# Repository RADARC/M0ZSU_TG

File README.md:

# M0ZSU_TG

Homebrew tracking generator for HP 8558B Spectrum Analyser.

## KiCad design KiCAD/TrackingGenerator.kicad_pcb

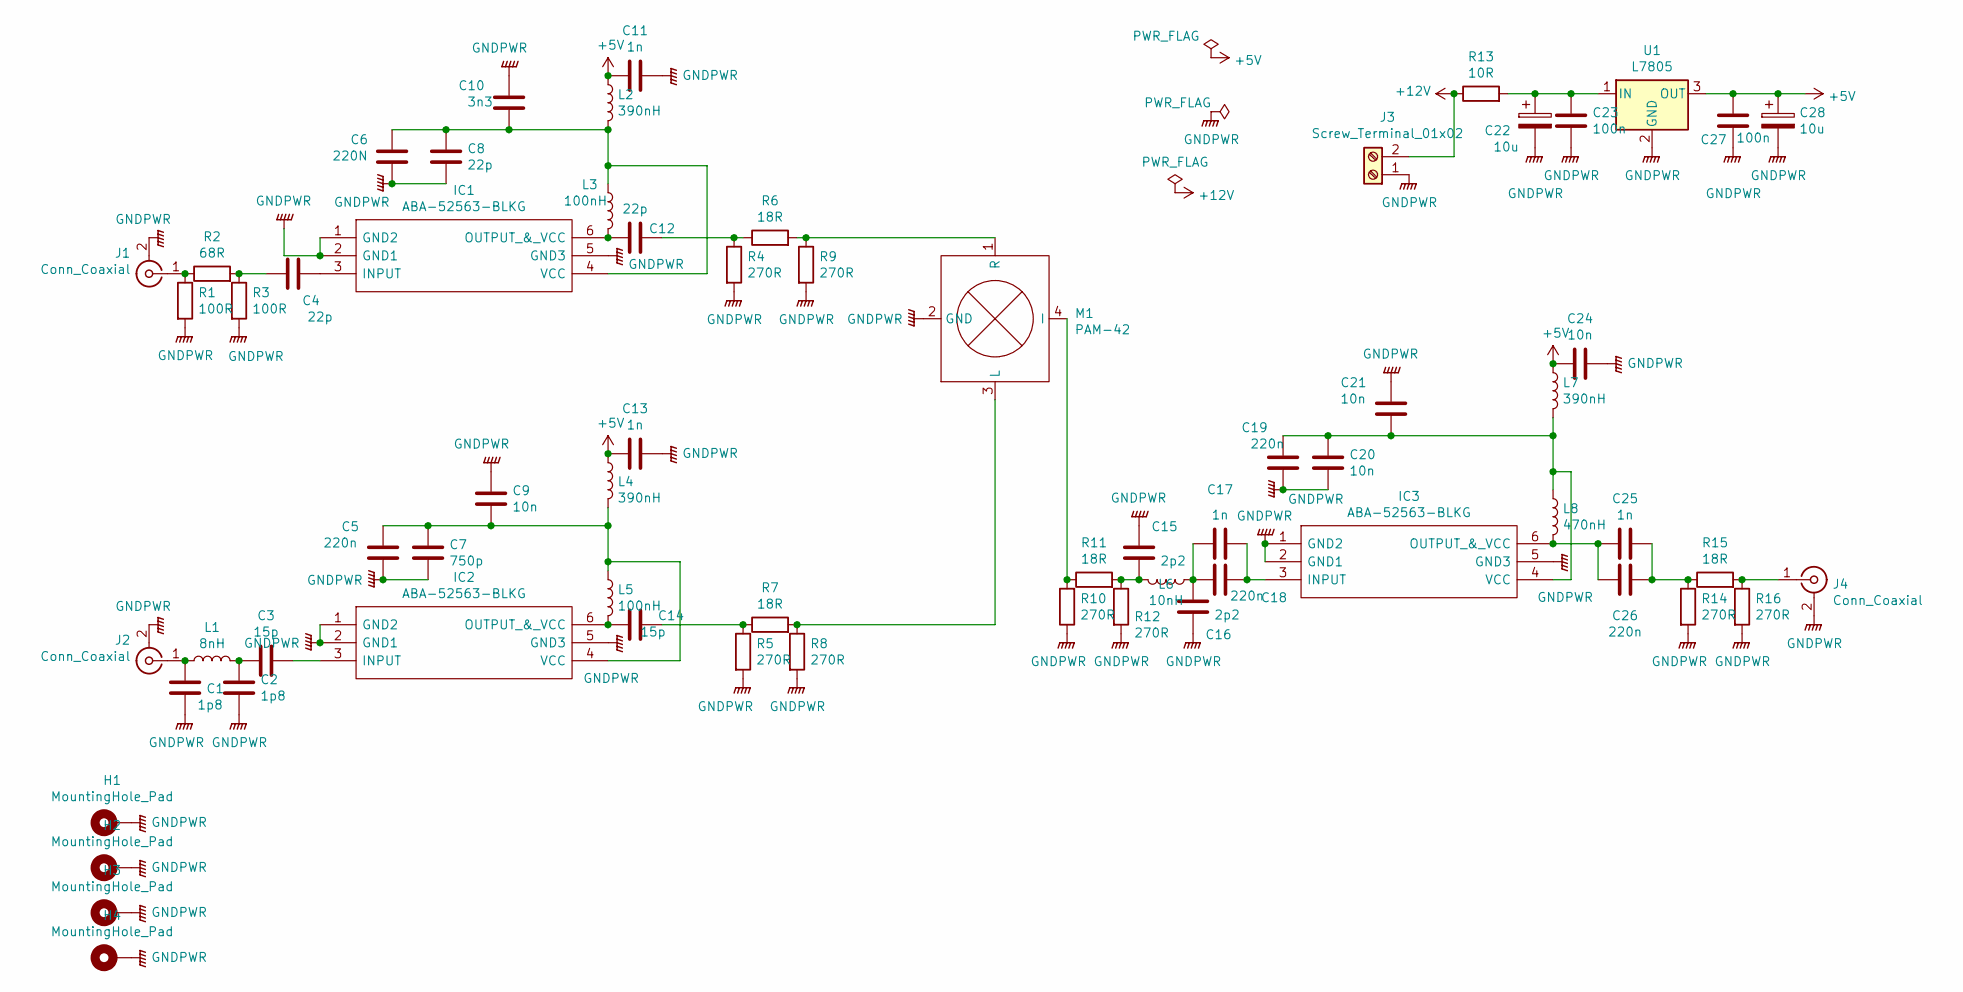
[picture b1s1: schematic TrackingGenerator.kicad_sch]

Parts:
C1, C2: 1p8; C_0603_1608Metric_Pad1.08x0.95mm_HandSolder
C3, C14: 15p; C_0603_1608Metric_Pad1.08x0.95mm_HandSolder
C4, C8, C12: 22p; C_0603_1608Metric_Pad1.08x0.95mm_HandSolder
C5, C18, C19, C26: 220n; C_0603_1608Metric_Pad1.08x0.95mm_HandSolder
C6: 220N; C_0603_1608Metric_Pad1.08x0.95mm_HandSolder
C7: 750p; C_0603_1608Metric_Pad1.08x0.95mm_HandSolder
C9, C20, C21, C24: 10n; C_0603_1608Metric_Pad1.08x0.95mm_HandSolder
C10: 3n3; C_0603_1608Metric_Pad1.08x0.95mm_HandSolder
C11, C13, C17, C25: 1n; C_0603_1608Metric_Pad1.08x0.95mm_HandSolder
C15, C16: 2p2; C_0603_1608Metric_Pad1.08x0.95mm_HandSolder
C22, C28: 10u; CP_Radial_D6.3mm_P2.50mm
C23, C27: 100n; C_0603_1608Metric_Pad1.08x0.95mm_HandSolder
H1, H2, H3, H4: MountingHole_Pad; MountingHole_3.2mm_M3_DIN965
IC1, IC2, IC3: ABA-52563-BLKG; SOT65P210X110-6N; Manufacturer_Part_Number ABA-52563-BLKG; Mouser Part Number 630-ABA-52563-BLKG
J1, J2, J4: Conn_Coaxial; SMA_Amphenol_132289_EdgeMount
J3: Screw_Terminal_01x02; TerminalBlock_TE_282834-2_1x02_P2.54mm_Horizontal
L1: 8nH; L_0603_1608Metric_Pad1.05x0.95mm_HandSolder
L2, L4, L7: 390nH; L_0603_1608Metric_Pad1.05x0.95mm_HandSolder
L3, L5: 100nH; L_0603_1608Metric_Pad1.05x0.95mm_HandSolder
L6: 10nH; L_0603_1608Metric_Pad1.05x0.95mm_HandSolder
L8: 470nH; L_0603_1608Metric_Pad1.05x0.95mm_HandSolder
M1: PAM-42; PAM42-Solder
R1, R3: 100R; R_0603_1608Metric_Pad0.98x0.95mm_HandSolder
R2: 68R; R_0603_1608Metric_Pad0.98x0.95mm_HandSolder
R4, R5, R8, R9, R10, R12, R14, R16: 270R; R_0603_1608Metric_Pad0.98x0.95mm_HandSolder
R6, R7, R11, R15: 18R; R_0603_1608Metric_Pad0.98x0.95mm_HandSolder
R13: 10R; R_Axial_DIN0411_L9.9mm_D3.6mm_P25.40mm_Horizontal
U1: L7805; TO-220-3_Vertical

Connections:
+5V: C11.1, C13.2, C24.2, C27.1, C28.1, L2.1, L4.1, L7.1, U1.3 (OUT)
+12V: J3.2, R13.1
GNDPWR: C1.2, C2.2, C5.2, C6.2, C7.2, C8.2, C9.1, C10.1, C11.2, C13.1, C15.1, C16.2, C19.2, C20.2, C21.1, C22.2, C23.2, C24.1, C27.2, C28.2, H1.1, H2.1, H3.1, H4.1, IC1.1 (GND2), IC1.2 (GND1), IC1.5 (GND3), IC2.1 (GND2), IC2.2 (GND1), IC2.5 (GND3), IC3.1 (GND2), IC3.2 (GND1), IC3.5 (GND3), J1.2 (Ext), J2.2 (Ext), J3.1, J4.2 (Ext), M1.2 (GND), R1.2, R3.2, R4.2, R5.2, R8.2, R9.2, R10.1, R12.2, R14.2, R16.2, U1.2 (GND)
unnamed: C1.1, J2.1 (In), L1.1
unnamed: C2.1, C3.1, L1.2
unnamed: C3.2, IC2.3 (INPUT)
unnamed: C4.1, R2.2, R3.1
unnamed: C4.2, IC1.3 (INPUT)
unnamed: C5.1, C7.1, C9.2, IC2.4 (VCC), L4.2, L5.1
unnamed: C6.1, C8.1, C10.2, IC1.4 (VCC), L2.2, L3.1
unnamed: C12.1, R4.1, R6.1
unnamed: C12.2, IC1.6 (OUTPUT_&_VCC), L3.2
unnamed: C14.1, IC2.6 (OUTPUT_&_VCC), L5.2
unnamed: C14.2, R5.1, R7.1
unnamed: C15.2, L6.2, R11.2, R12.1
unnamed: C16.1, C17.1, C18.1, L6.1
unnamed: C17.2, C18.2, IC3.3 (INPUT)
unnamed: C19.1, C20.1, C21.2, IC3.4 (VCC), L7.2, L8.1
unnamed: C22.1, C23.1, R13.2, U1.1 (IN)
unnamed: C25.1, C26.1, IC3.6 (OUTPUT_&_VCC), L8.2
unnamed: C25.2, C26.2, R14.1, R15.1
unnamed: J1.1 (In), R1.1, R2.1
unnamed: J4.1 (In), R15.2, R16.1
unnamed: M1.1 (R), R6.2, R9.1
unnamed: M1.3 (L), R7.2, R8.1
unnamed: M1.4 (I), R10.2, R11.1

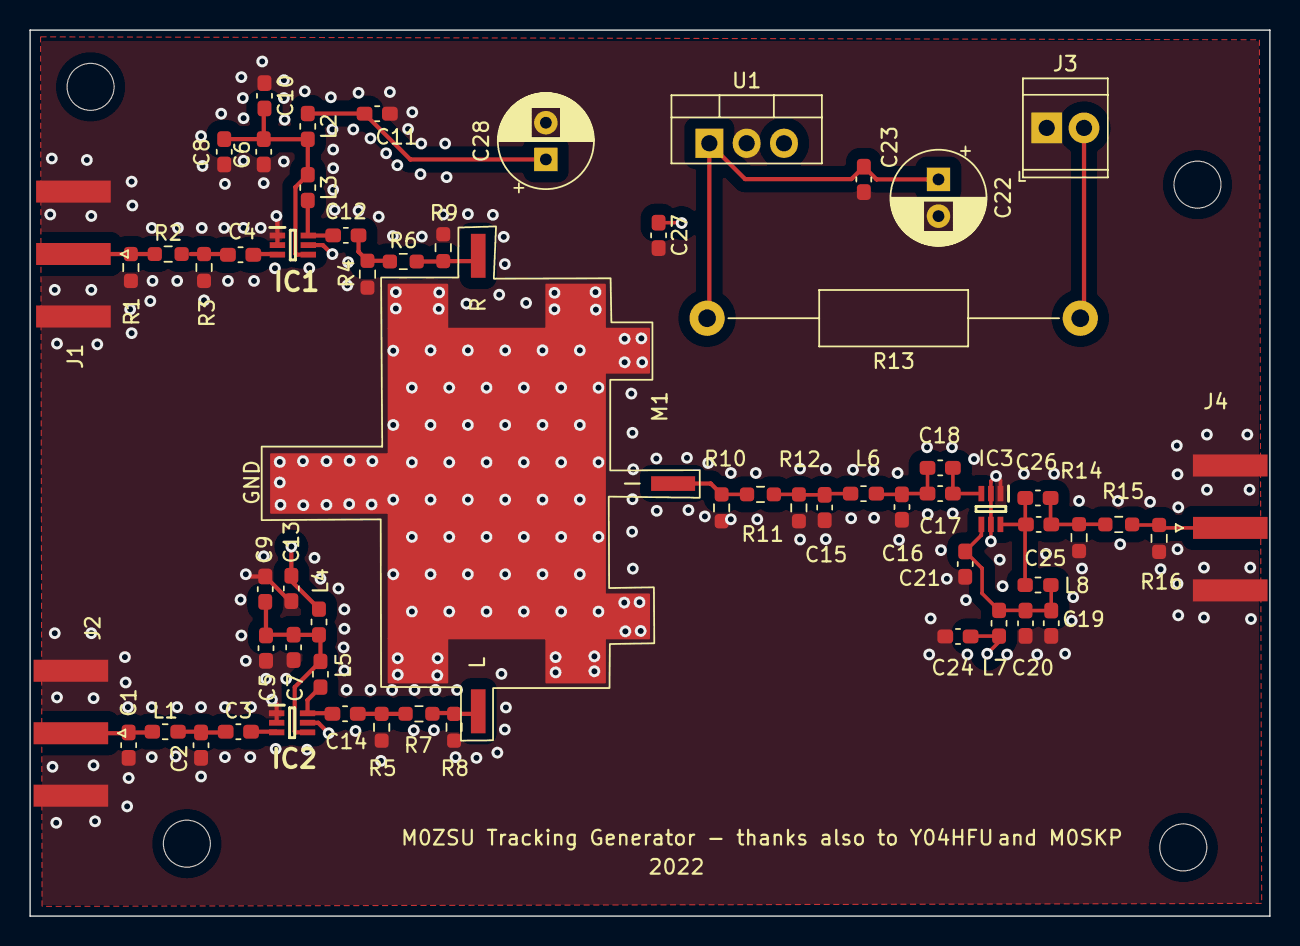
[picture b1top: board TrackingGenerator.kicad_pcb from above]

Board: 4 copper layers, 84.4 x 60.3 mm, 65 parts (0 on the bottom side), 26 nets.

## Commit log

2022-01-18 Added KiCad files
    Added KiCad files initial.
2022-01-21 Changes to use LC7628 stackup
2022-01-21 More routing work
2022-01-25 Add more routing
2022-01-25 Further updates
2022-01-26 New Branch for Richard's Ideas
2022-01-27 Further work compacting and tidying
2022-02-02 Further routing and stitching
2022-02-07 Update Footprint for PAM-42 and update pcb layout to use it
2022-02-07 PCB Update
2022-02-08 Gerber generation
2022-02-10 Added PCB text
2022-02-10 Update Gerbers
